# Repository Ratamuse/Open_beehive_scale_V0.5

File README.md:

# Open_beehive_scale_V0.5
Nb_Iot version

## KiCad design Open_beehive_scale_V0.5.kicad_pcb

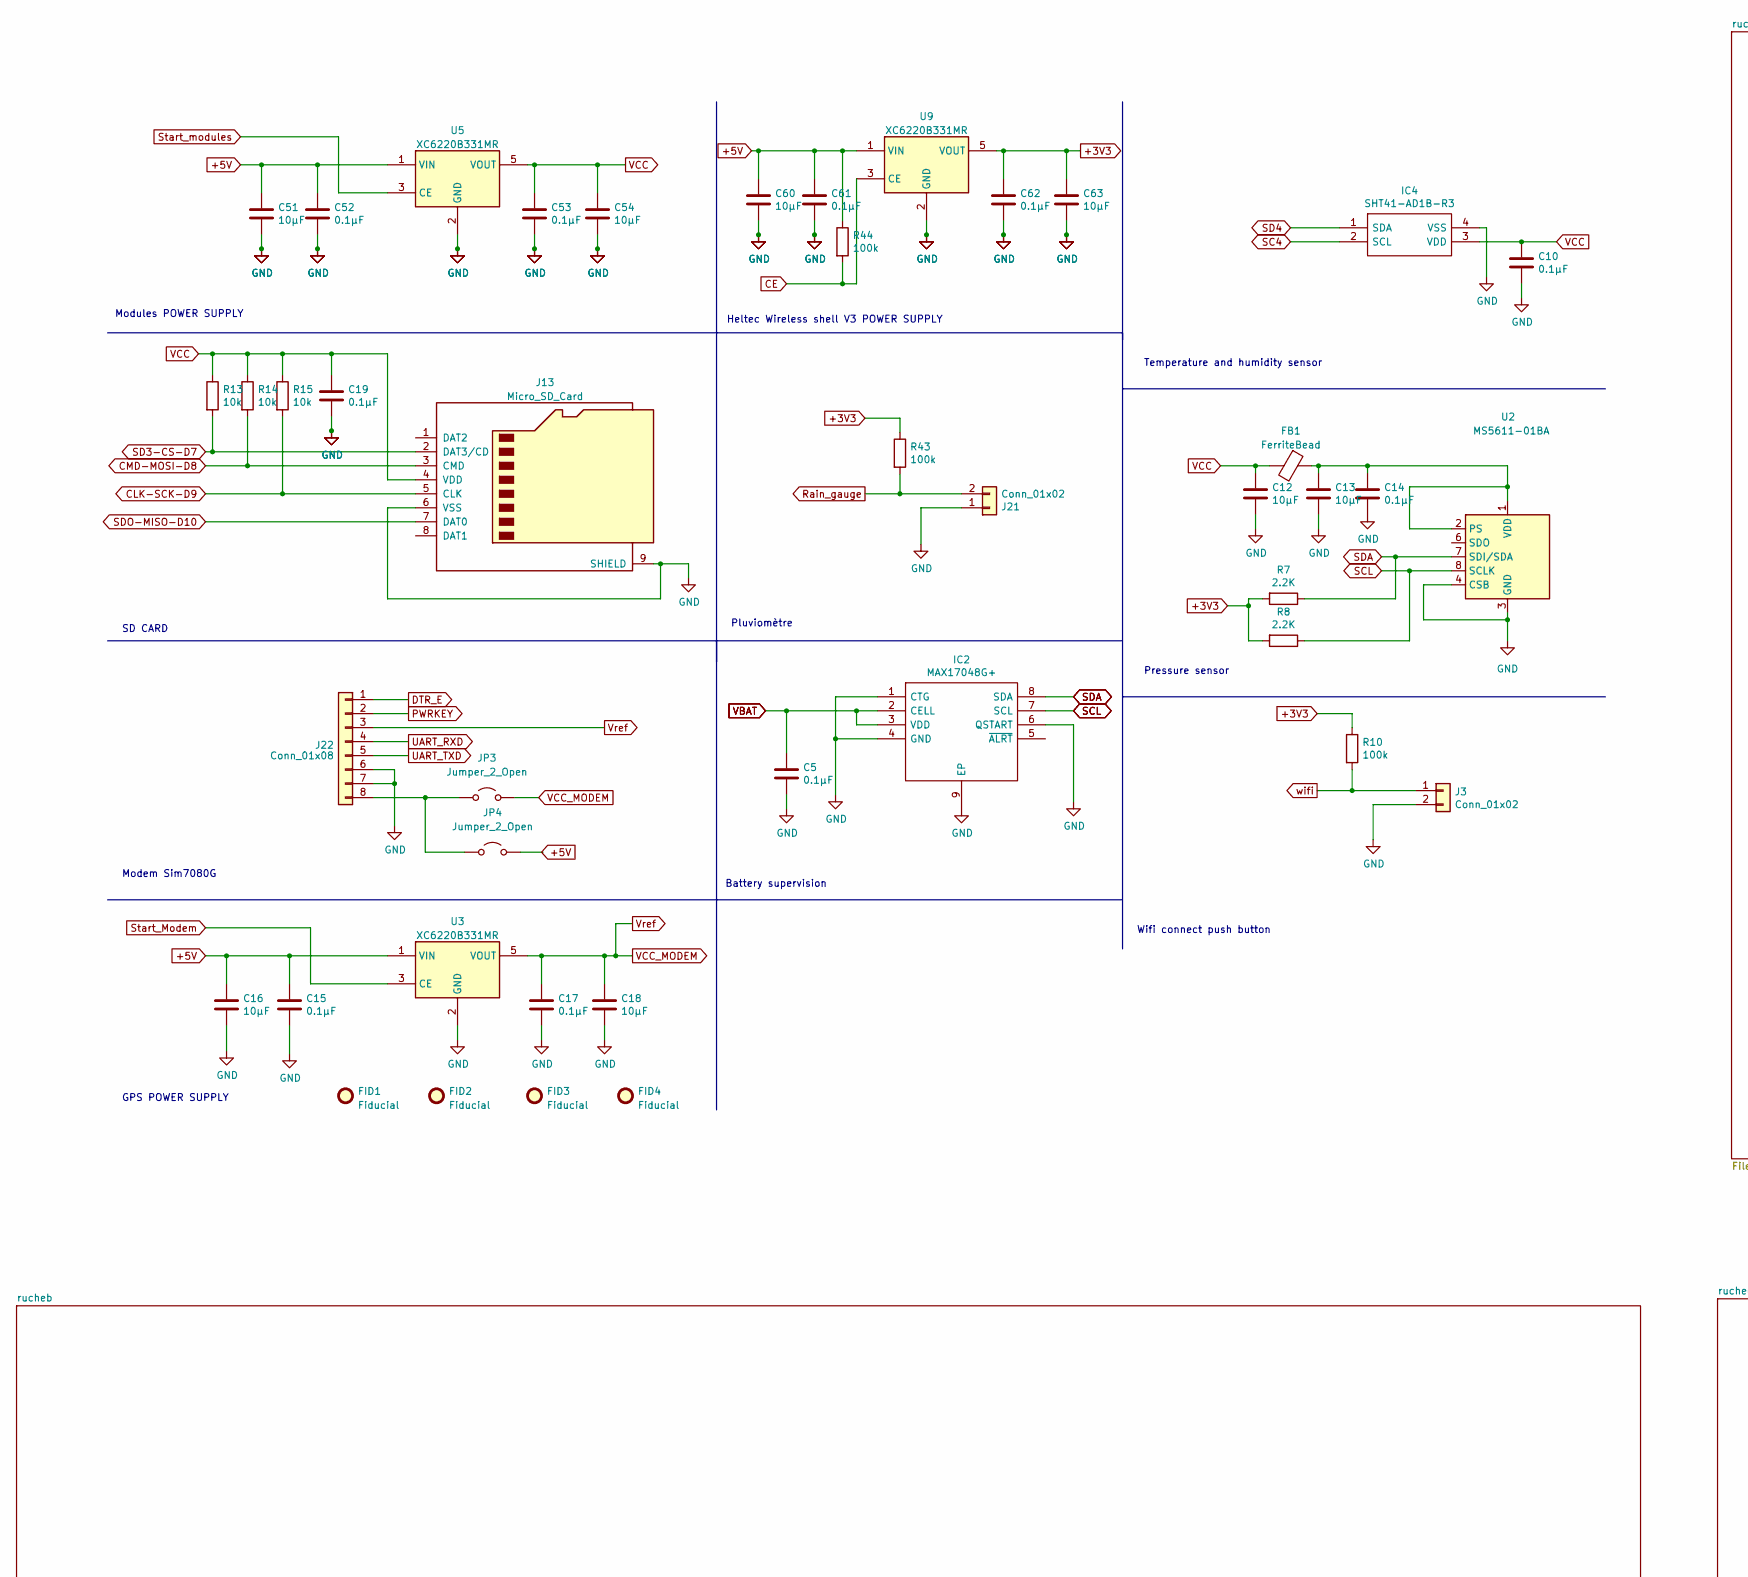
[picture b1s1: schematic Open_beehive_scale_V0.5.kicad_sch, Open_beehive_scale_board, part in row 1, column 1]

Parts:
C5, C10, C14, C17, C19, C52, C53, C61, C62: 0.1µF; C_0603_1608Metric
C12, C13, C18, C51, C54, C60, C63: 10µF; C_0805_2012Metric
C15: 0.1µF; C_0805_2012Metric
C16: 10µF; C_0603_1608Metric
FB1: FerriteBead; R_0603_1608Metric
FID1, FID2, FID3, FID4: Fiducial; Fiducial_1mm_Mask3mm
IC2: MAX17048G+; SON50P200X200X80-9N-D; Manufacturer_Part_Number MAX17048G+; Mouser Part Number 700-MAX17048G+
IC4: SHT41-AD1B-R3; SHT41AD1BR3; Manufacturer_Part_Number SHT41-AD1B-R3; Mouser Part Number 403-SHT41-AD1B-R3
J3, J21: Conn_01x02; 1725656
J13: Micro_SD_Card; microSD_HC_Hirose_DM3AT-SF-PEJM5
J22: Conn_01x08; Sim8070G
JP3, JP4: Jumper_2_Open; SolderJumper-2_P1.3mm_Open_RoundedPad1.0x1.5mm
R7, R8: 2.2K; R_0603_1608Metric
R10, R43, R44: 100k; R_0603_1608Metric
R13, R14, R15: 10k; R_0603_1608Metric
U2: MS5611-01BA; LGA-8_3x5mm_P1.25mm
U3, U5, U9: XC6220B331MR; SOT-23-5

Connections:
+3V3: C62.1, C63.1, R7.2, R8.2, R10.1, R43.1, U9.5 (VOUT); also elsewhere on the board
+5V: C15.1, C16.1, C51.1, C52.1, C60.1, C61.1, JP4.2 (B), R44.1, U3.1 (VIN), U5.1 (VIN), U9.1 (VIN); also elsewhere on the board
CE: R44.2, U9.3 (CE); also elsewhere on the board
CLK-SCK-D9: J13.5 (CLK), R15.2; also elsewhere on the board
CMD-MOSI-D8: J13.3 (CMD), R14.2; also elsewhere on the board
DTR_E: J22.1; also elsewhere on the board
GND: C5.2, C10.2, C12.2, C13.2, C14.2, C15.2, C16.2, C17.2, C18.2, C19.2, C51.2, C52.2, C53.2, C54.2, C60.2, C61.2, C62.2, C63.2, IC2.1 (CTG), IC2.4 (GND), IC2.6 (QSTART), IC2.9 (EP), IC4.4 (VSS), J3.2, J13.6 (VSS), J13.9 (SHIELD), J21.1, J22.6, J22.7, U2.3 (GND), U2.4 (CSB), U2.5 (CSB), U3.2 (GND), U5.2 (GND), U9.2 (GND); also elsewhere on the board
unnamed: J22.8, JP3.1 (A), JP4.1 (A)
unnamed: C13.1, C14.1, FB1.1, U2.1 (VDD), U2.2 (PS)
PWRKEY: J22.2; also elsewhere on the board
Rain_gauge: J21.2, R43.2; also elsewhere on the board
SC4: IC4.2 (SCL); also elsewhere on the board
SCL: IC2.7 (SCL), R8.1, U2.8 (SCLK); also elsewhere on the board
SD3-CS-D7: J13.2 (DAT3/CD), R13.2; also elsewhere on the board
SD4: IC4.1 (SDA); also elsewhere on the board
SDA: IC2.8 (SDA), R7.1, U2.7 (SDI/SDA); also elsewhere on the board
SDO-MISO-D10: J13.7 (DAT0); also elsewhere on the board
Start_Modem: U3.3 (CE); also elsewhere on the board
Start_modules: U5.3 (CE); also elsewhere on the board
UART_RXD: J22.4; also elsewhere on the board
UART_TXD: J22.5; also elsewhere on the board
VBAT: C5.1, IC2.2 (CELL), IC2.3 (VDD); also elsewhere on the board
VCC: C10.1, C12.1, C19.1, C53.1, C54.1, FB1.2, IC4.3 (VDD), J13.4 (VDD), R13.1, R14.1, R15.1, U5.5 (VOUT); also elsewhere on the board
VCC_MODEM: C17.1, C18.1, J22.3, JP3.2 (B), U3.5 (VOUT)
wifi: J3.1, R10.2; also elsewhere on the board

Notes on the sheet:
SD CARD
Pluviomètre
Modem Sim7080G
Battery supervision
Heltec Wireless shell V3 POWER SUPPLY
Wifi connect push button
Temperature and humidity sensor
Pressure sensor
Modules POWER SUPPLY
GPS POWER SUPPLY

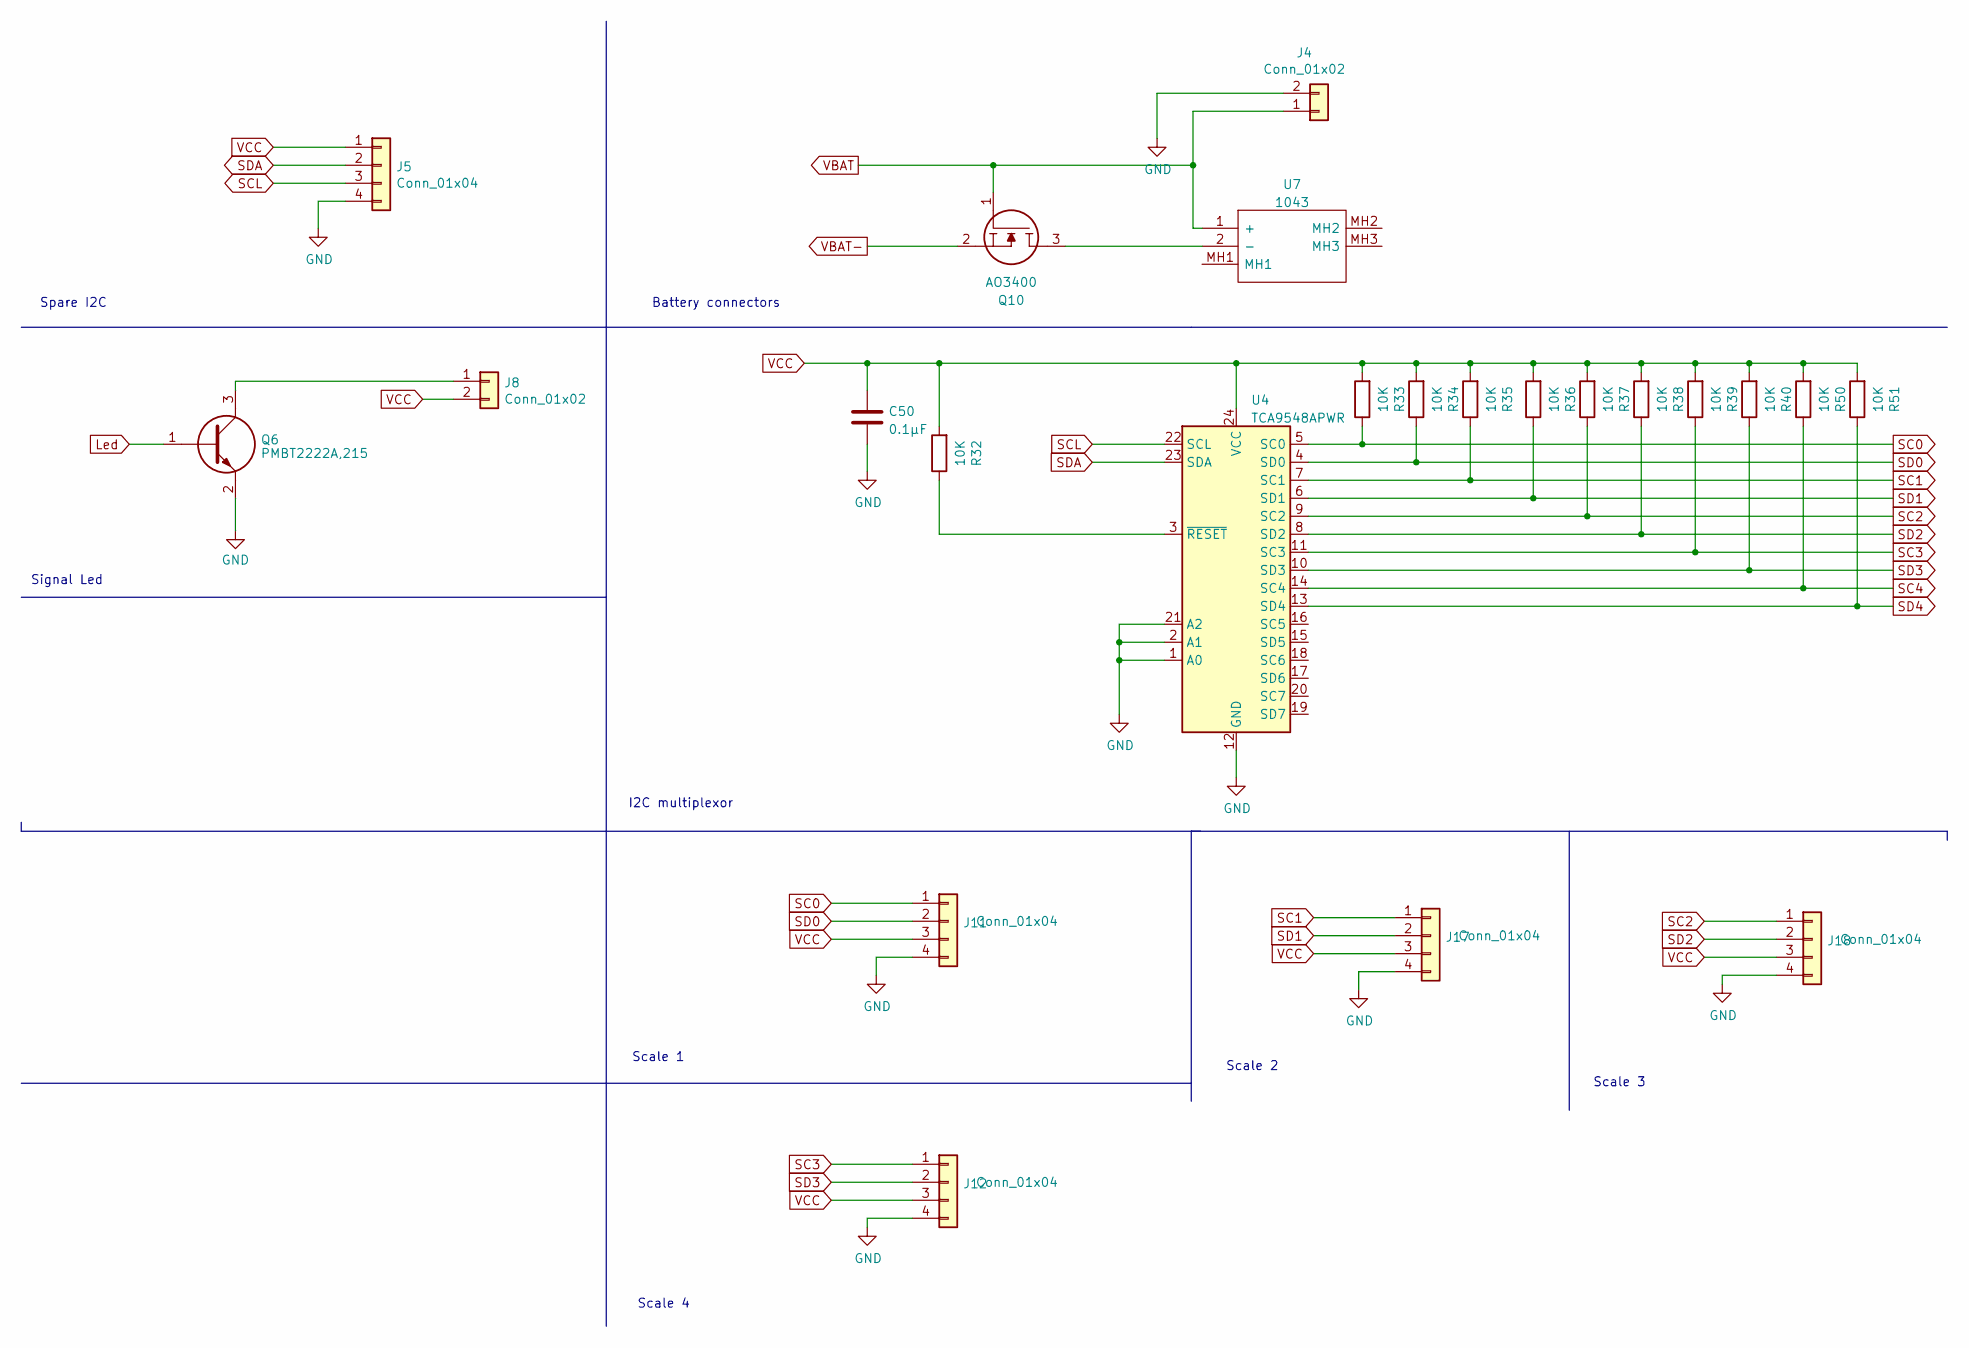
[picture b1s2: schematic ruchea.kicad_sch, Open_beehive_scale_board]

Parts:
C50: 0.1µF; C_0603_1608Metric
J4: Conn_01x02; JST_PH_B2B-PH-K_1x02_P2.00mm_Vertical
J5, J11, J12, J17, J18: Conn_01x04; 1725672
J8: Conn_01x02; 1725656
Q6: PMBT2222A,215; PMBT2222A215; Mouser Part Number 771-PMBT2222A-T/R
Q10: AO3400; SOT-23; Manufacturer_Part_Number AO3400
R32, R33, R34, R35, R36, R37, R38, R39, R40, R50, R51: 10K; R_0603_1608Metric
U4: TCA9548APWR; TSSOP-24_4.4x7.8mm_P0.65mm
U7: 1043; Mouser Part Number 534-1043

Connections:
GND: C50.2, J4.2, J5.4, J11.4, J12.4, J17.4, J18.4, Q6.2, U4.1 (A0), U4.2 (A1), U4.12 (GND), U4.21 (A2); also elsewhere on the board
Led: Q6.1; also elsewhere on the board
unnamed: J8.1, Q6.3
unnamed: R32.1, U4.3 (~RESET)
unnamed: Q10.3, U7.2 (-)
SC0: J11.1, R33.1, U4.5 (SC0)
SC1: J17.1, R35.1, U4.7 (SC1)
SC2: J18.1, R37.1, U4.9 (SC2)
SC3: J12.1, R39.1, U4.11 (SC3)
SC4: R50.1, U4.14 (SC4); also elsewhere on the board
SCL: J5.3, U4.22 (SCL); also elsewhere on the board
SD0: J11.2, R34.1, U4.4 (SD0)
SD1: J17.2, R36.1, U4.6 (SD1)
SD2: J18.2, R38.1, U4.8 (SD2)
SD3: J12.2, R40.1, U4.10 (SD3)
SD4: R51.1, U4.13 (SD4); also elsewhere on the board
SDA: J5.2, U4.23 (SDA); also elsewhere on the board
VBAT: J4.1, Q10.1, U7.1 (+); also elsewhere on the board
VBAT-: Q10.2; also elsewhere on the board
VCC: C50.1, J5.1, J8.2, J11.3, J12.3, J17.3, J18.3, R32.2, R33.2, R34.2, R35.2, R36.2, R37.2, R38.2, R39.2, R40.2, R50.2, R51.2, U4.24 (VCC); also elsewhere on the board

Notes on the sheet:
Scale 4
Scale 1
Scale 3
Scale 2
I2C multiplexor
Battery connectors
Spare I2C
Signal Led

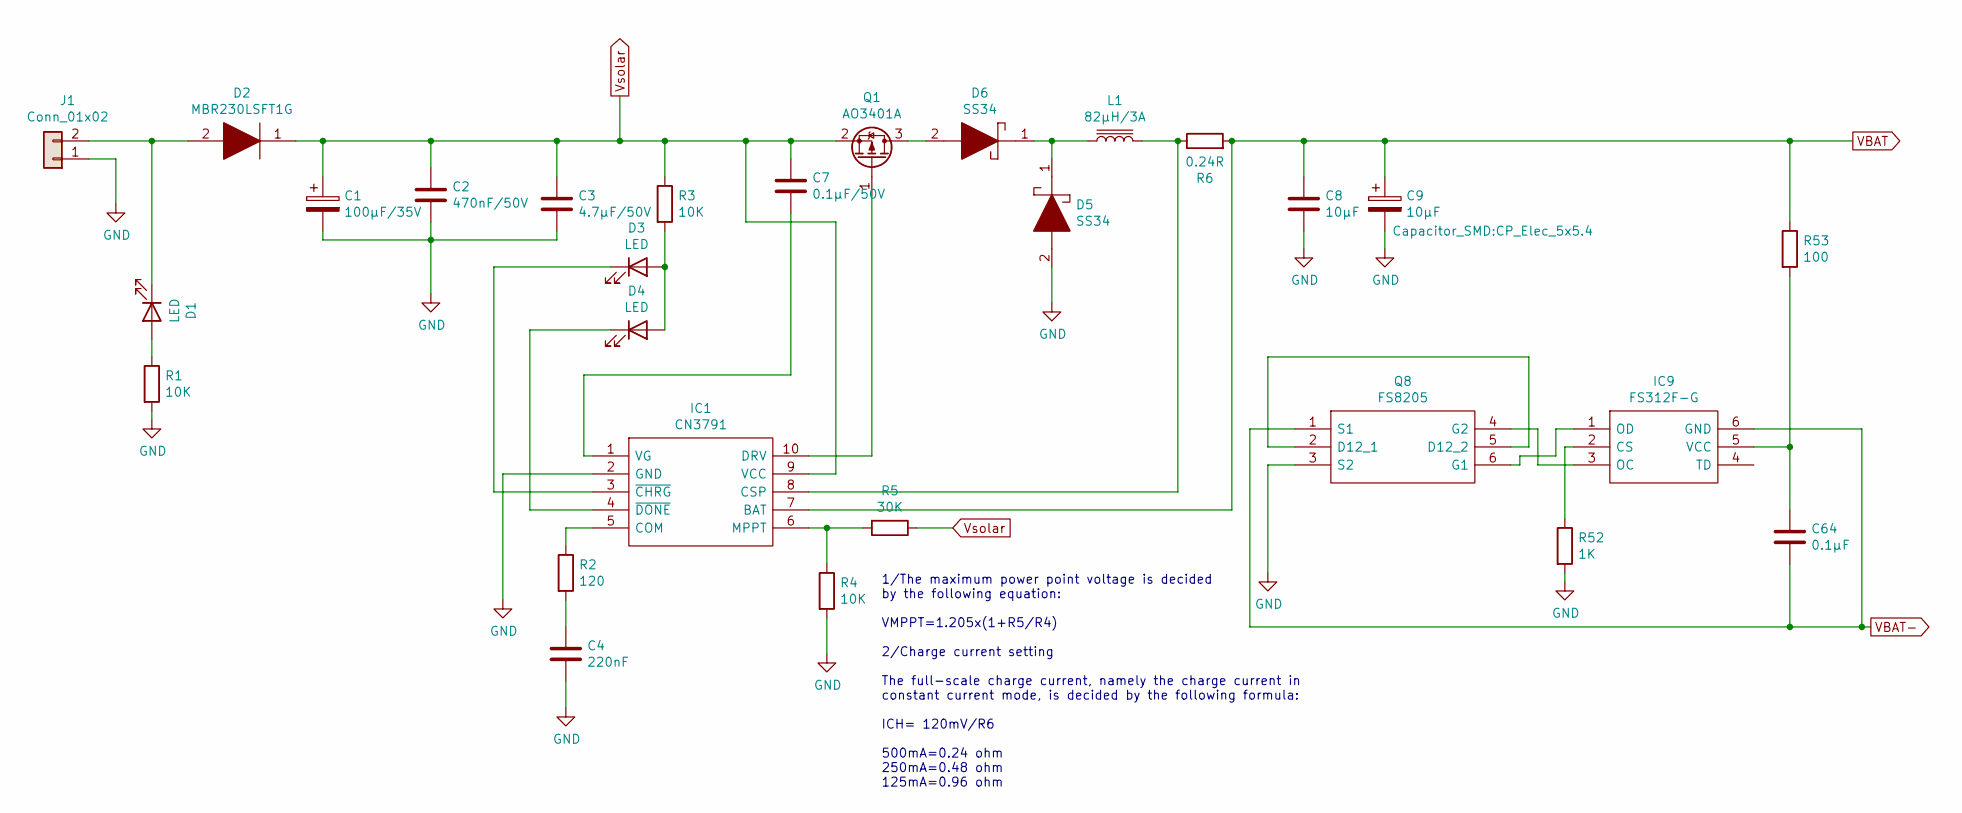
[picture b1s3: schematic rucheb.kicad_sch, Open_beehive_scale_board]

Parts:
C1: 100µF/35V; CP_Elec_6.3x7.7
C2: 470nF/50V; C_0603_1608Metric
C3: 4.7µF/50V; C_0805_2012Metric
C4: 220nF; C_0603_1608Metric
C7: 0.1µF/50V; C_0603_1608Metric
C8: 10µF; C_0805_2012Metric
C9: 10µF; CP_Elec_5x5.4
C64: 0.1µF; C_0603_1608Metric
D1, D3, D4: LED; LED_0603_1608Metric_Pad1.05x0.95mm_HandSolder
D2: MBR230LSFT1G; SODFL3616X98N; Manufacturer_Part_Number MBR230LSFT1G; Mouser Part Number 863-MBR230LSFT1G
D5, D6: SS34; DIOM8059X256N; Manufacturer_Part_Number SS34; Mouser Part Number 512-SS34
IC1: CN3791; SOP100P600X175-10N; Manufacturer_Part_Number CN3791
IC9: FS312F-G; SOT95P280X145-6N; Manufacturer_Part_Number FS312F-G
J1: Conn_01x02; SHDR2W90P0X500_1X2_1060X980X1380P
L1: 82µH/3A; INDPM138126X700N
Q1: AO3401A; SOT-23
Q8: FS8205; Manufacturer_Part_Number FS8205
R1, R3, R4: 10K; R_0603_1608Metric
R2: 120; R_0603_1608Metric
R5: 30K; R_0603_1608Metric
R6: 0.24R; R_2512_6332Metric
R52: 1K; R_0603_1608Metric
R53: 100; R_0603_1608Metric

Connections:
GND: C1.2, C2.2, C3.2, C4.2, C8.2, C9.2, D5.2, IC1.2 (GND), J1.1, Q8.3 (S2), R1.2, R4.2, R52.2; also elsewhere on the board
unnamed: C4.1, R2.2
unnamed: D1.2 (A), R1.1
unnamed: D1.1 (K), D2.2, J1.2
unnamed: D3.2 (A), D4.2 (A), R3.2
unnamed: D3.1 (K), IC1.3 (~CHRG)
unnamed: D4.1 (K), IC1.4 (~DONE)
unnamed: D5.1, D6.1, L1.1
unnamed: IC1.5 (COM), R2.1
unnamed: IC1.8 (CSP), L1.2, R6.1
unnamed: IC1.10 (DRV), Q1.1 (G)
unnamed: IC1.6 (MPPT), R4.1, R5.2
unnamed: C7.2, IC1.1 (VG)
unnamed: IC9.2 (CS), R52.1
unnamed: IC9.3 (OC), Q8.4 (G2)
unnamed: IC9.1 (OD), Q8.6 (G1)
unnamed: C64.1, IC9.5 (VCC), R53.2
unnamed: D6.2, Q1.3 (D)
unnamed: Q8.2 (D12_1), Q8.5 (D12_2)
VBAT: C8.1, C9.1, IC1.7 (BAT), R6.2, R53.1; also elsewhere on the board
VBAT-: C64.2, IC9.6 (GND), Q8.1 (S1); also elsewhere on the board
Vsolar: C1.1, C2.1, C3.1, C7.1, D2.1, IC1.9 (VCC), Q1.2 (S), R3.1, R5.1

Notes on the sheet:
1/The maximum power point voltage is decided by the following equation: VMPPT=1.205x(1+R5/R4) 2/Charge current setting The full-scale charge current, namely the charge current in constant current mode, is decided by the following formula: ICH= 120mV/R6 500mA=0.24 ohm 250mA=0.48 ohm 125mA=0.96 ohm

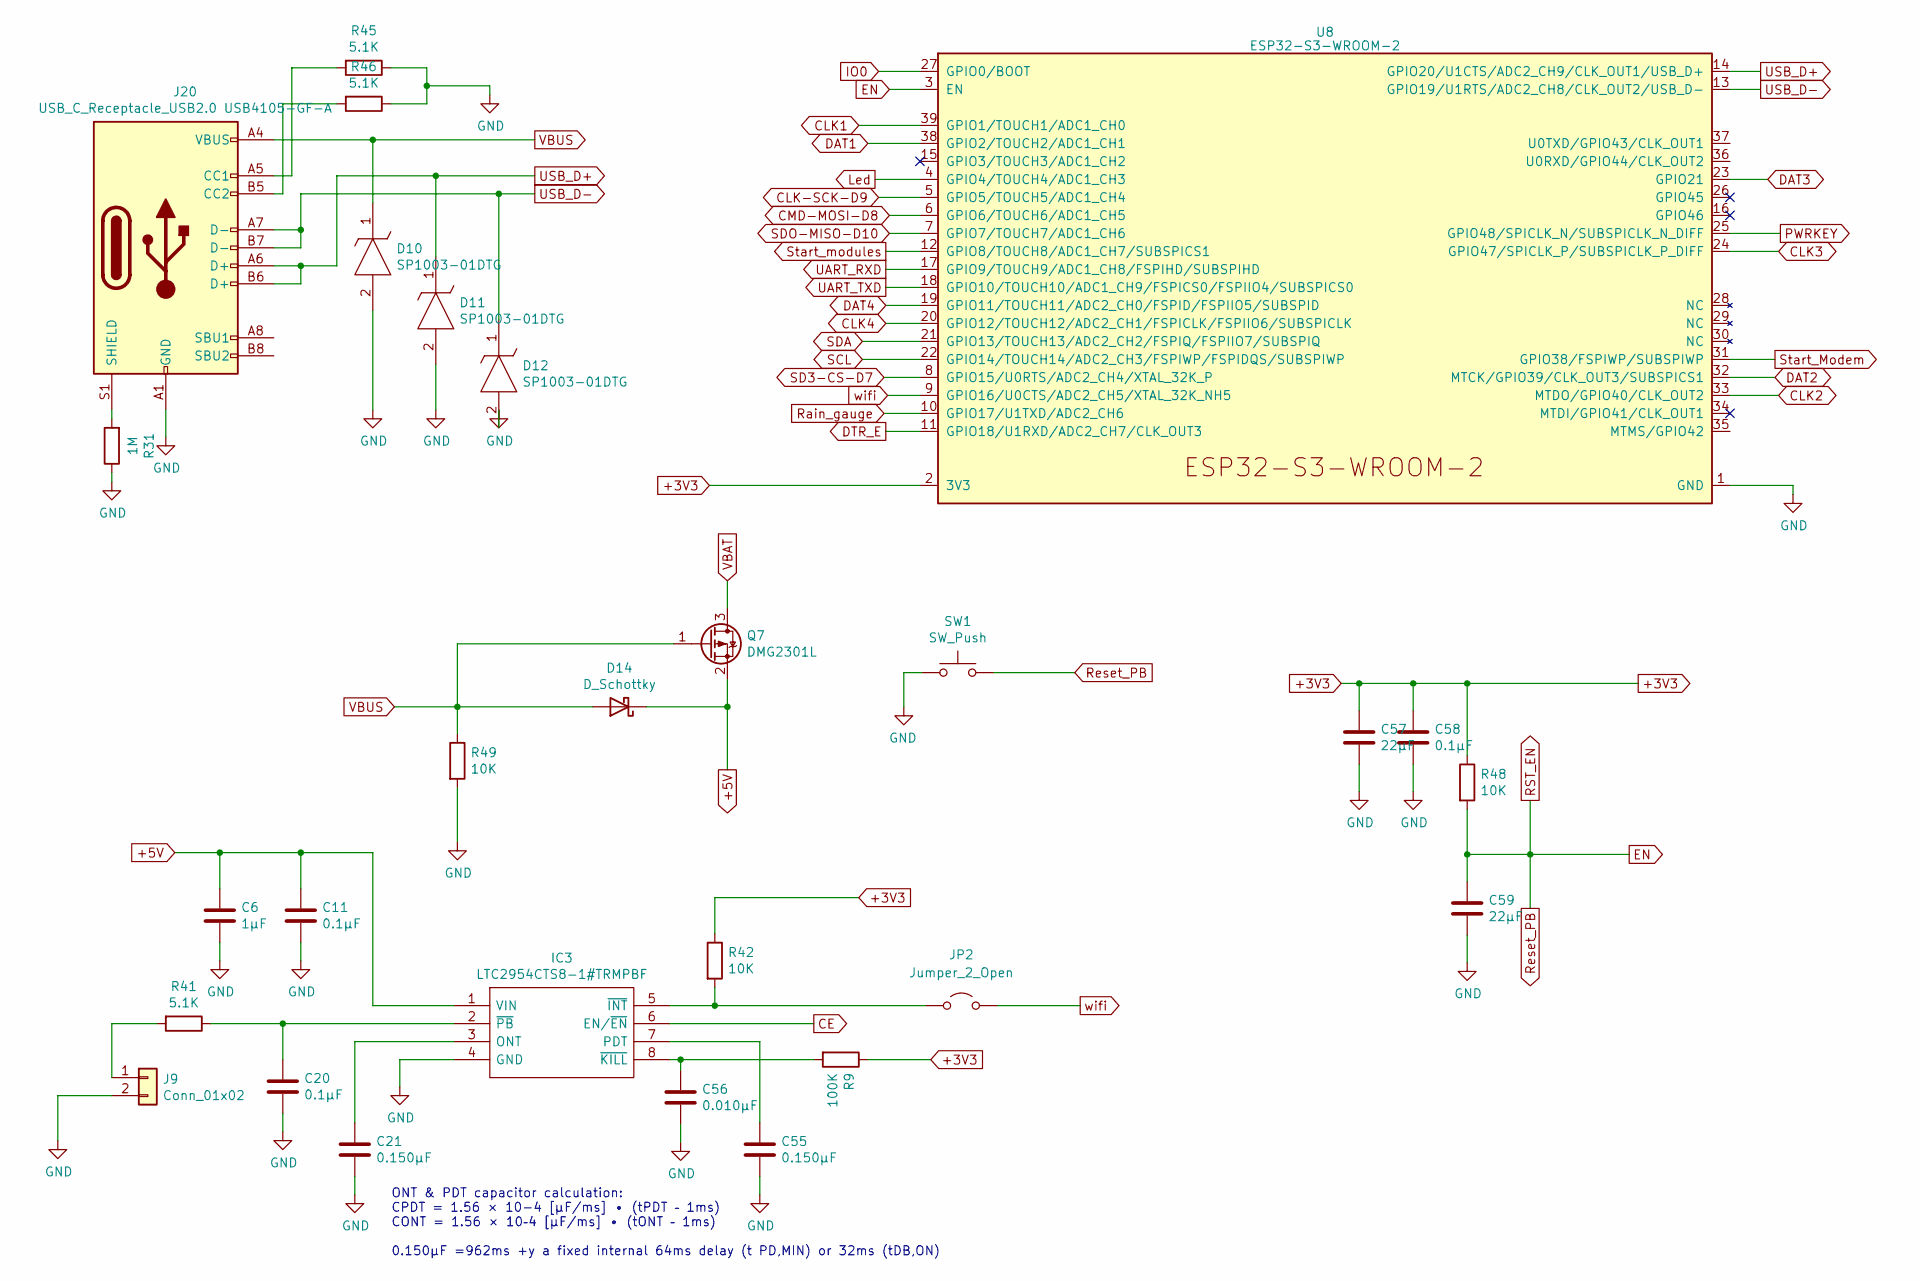
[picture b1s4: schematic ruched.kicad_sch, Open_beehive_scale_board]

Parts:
C6: 1µF; C_0603_1608Metric
C11, C20, C58: 0.1µF; C_0603_1608Metric
C21, C55: 0.150µF; C_0603_1608Metric
C56: 0.010µF; C_0603_1608Metric
C57, C59: 22µF; C_0805_2012Metric
D10, D11, D12: SP1003-01DTG; SODFL1406X65N; Manufacturer_Part_Number SP1003-01DTG; Mouser Part Number 576-SP1003-01DTG
D14: D_Schottky; D_SOD-323
IC3: LTC2954CTS8-1#TRMPBF; SOT65P280X100-8N; Manufacturer_Part_Number LTC2954CTS8-1#TRMPBF; Mouser Part Number 584-C2954CTS8-1TMPF
J9: Conn_01x02; 1725656
J20: USB_C_Receptacle_USB2.0 USB4105-GF-A; TYPE-C-31-M-12
JP2: Jumper_2_Open; SolderJumper-2_P1.3mm_Open_RoundedPad1.0x1.5mm
Q7: DMG2301L; SOT-23
R9: 100K; R_0603_1608Metric
R31: 1M; R_0603_1608Metric
R41, R45, R46: 5.1K; R_0603_1608Metric
R42, R48, R49: 10K; R_0603_1608Metric
SW1: SW_Push; PTS636SL43SMTRLFS
U8: ESP32-S3-WROOM-2

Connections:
+3V3: C57.1, C58.1, R9.1, R42.1, R48.1, U8.2 (3V3); also elsewhere on the board
+5V: C6.1, C11.1, D14.1 (K), IC3.1 (VIN), Q7.2 (S); also elsewhere on the board
CE: IC3.6 (EN/~EN); also elsewhere on the board
CLK1: U8.39 (GPIO1/TOUCH1/ADC1_CH0); also elsewhere on the board
CLK2: U8.33 (MTDO/GPIO40/CLK_OUT2); also elsewhere on the board
CLK3: U8.24 (GPIO47/SPICLK_P/SUBSPICLK_P_DIFF); also elsewhere on the board
CLK4: U8.20 (GPIO12/TOUCH12/ADC2_CH1/FSPICLK/FSPIIO6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); also elsewhere on the board
CLK-SCK-D9: U8.5 (GPIO5/TOUCH5/ADC1_CH4); also elsewhere on the board
CMD-MOSI-D8: U8.6 (GPIO6/TOUCH6/ADC1_CH5); also elsewhere on the board
DAT1: U8.38 (GPIO2/TOUCH2/ADC1_CH1); also elsewhere on the board
DAT2: U8.32 (MTCK/GPIO39/CLK_OUT3/SUBSPICS1); also elsewhere on the board
DAT3: U8.23 (GPIO21); also elsewhere on the board
DAT4: U8.19 (GPIO11/TOUCH11/ADC2_CH0/FSPID/FSPIIO5/S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); also elsewhere on the board
DTR_E: U8.11 (GPIO18/U1RXD/ADC2_CH7/CLK_OUT3); also elsewhere on the board
EN: C59.1, R48.2, SW1.1, U8.3 (EN)
GND: C6.2, C11.2, C20.2, C21.2, C55.2, C56.2, C57.2, C58.2, C59.2, D10.2, D11.2, D12.2, IC3.4 (GND), J9.2, J20.A1 (GND), J20.A12 (GND), J20.B1 (GND), J20.B12 (GND), R31.1, R45.1, R46.1, R49.2, SW1.2, U8.1 (GND), U8.40 (GND), U8.41 (GND); also elsewhere on the board
IO0: U8.27 (GPIO0/BOOT)
Led: U8.4 (GPIO4/TOUCH4/ADC1_CH3); also elsewhere on the board
unnamed: C21.1, IC3.3 (ONT)
unnamed: C55.1, IC3.7 (PDT)
unnamed: IC3.5 (~INT), JP2.1 (A), R42.2
unnamed: C56.1, IC3.8 (~KILL), R9.2
unnamed: C20.1, IC3.2 (~PB), R41.1
unnamed: J9.1, R41.2
unnamed: J20.A5 (CC1), R45.2
unnamed: J20.B5 (CC2), R46.2
unnamed: J20.S1 (SHIELD), R31.2
PWRKEY: U8.25 (GPIO48/SPICLK_N/SUBSPICLK_N_DIFF); also elsewhere on the board
Rain_gauge: U8.10 (GPIO17/U1TXD/ADC2_CH6); also elsewhere on the board
SCL: U8.22 (GPIO14/TOUCH14/ADC2_CH3/FSPIWP/FSPIDQS/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); also elsewhere on the board
SD3-CS-D7: U8.8 (GPIO15/U0RTS/ADC2_CH4/XTAL_32K_P); also elsewhere on the board
SDA: U8.21 (GPIO13/TOUCH13/ADC2_CH2/FSPIQ/FSPIIO7/S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); also elsewhere on the board
SDO-MISO-D10: U8.7 (GPIO7/TOUCH7/ADC1_CH6); also elsewhere on the board
Start_Modem: U8.31 (GPIO38/FSPIWP/SUBSPIWP); also elsewhere on the board
Start_modules: U8.12 (GPIO8/TOUCH8/ADC1_CH7/SUBSPICS1); also elsewhere on the board
UART_RXD: U8.17 (GPIO9/TOUCH9/ADC1_CH8/FSPIHD/SUBSPIHD); also elsewhere on the board
UART_TXD: U8.18 (GPIO10/TOUCH10/ADC1_CH9/FSPICS0/FSPIIO4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); also elsewhere on the board
USB_D+: D11.1, J20.A6 (D+), J20.B6 (D+), U8.14 (GPIO20/U1CTS/ADC2_CH9/CLK_OUT1/USB_D+)
USB_D-: D12.1, J20.A7 (D-), J20.B7 (D-), U8.13 (GPIO19/U1RTS/ADC2_CH8/CLK_OUT2/USB_D-)
VBAT: Q7.3 (D); also elsewhere on the board
VBUS: D10.1, D14.2 (A), J20.A4 (VBUS), J20.A9 (VBUS), J20.B4 (VBUS), J20.B9 (VBUS), Q7.1 (G), R49.1
wifi: JP2.2 (B), U8.9 (GPIO16/U0CTS/ADC2_CH5/XTAL_32K_NH5); also elsewhere on the board

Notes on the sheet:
ONT & PDT capacitor calculation: CPDT = 1.56 × 10-4 [μF/ms] • (tPDT – 1ms) CONT = 1.56 × 10–4 [μF/ms] • (tONT – 1ms) 0.150µF =962ms +y a fixed internal 64ms delay (t PD,MIN) or 32ms (tDB,ON)

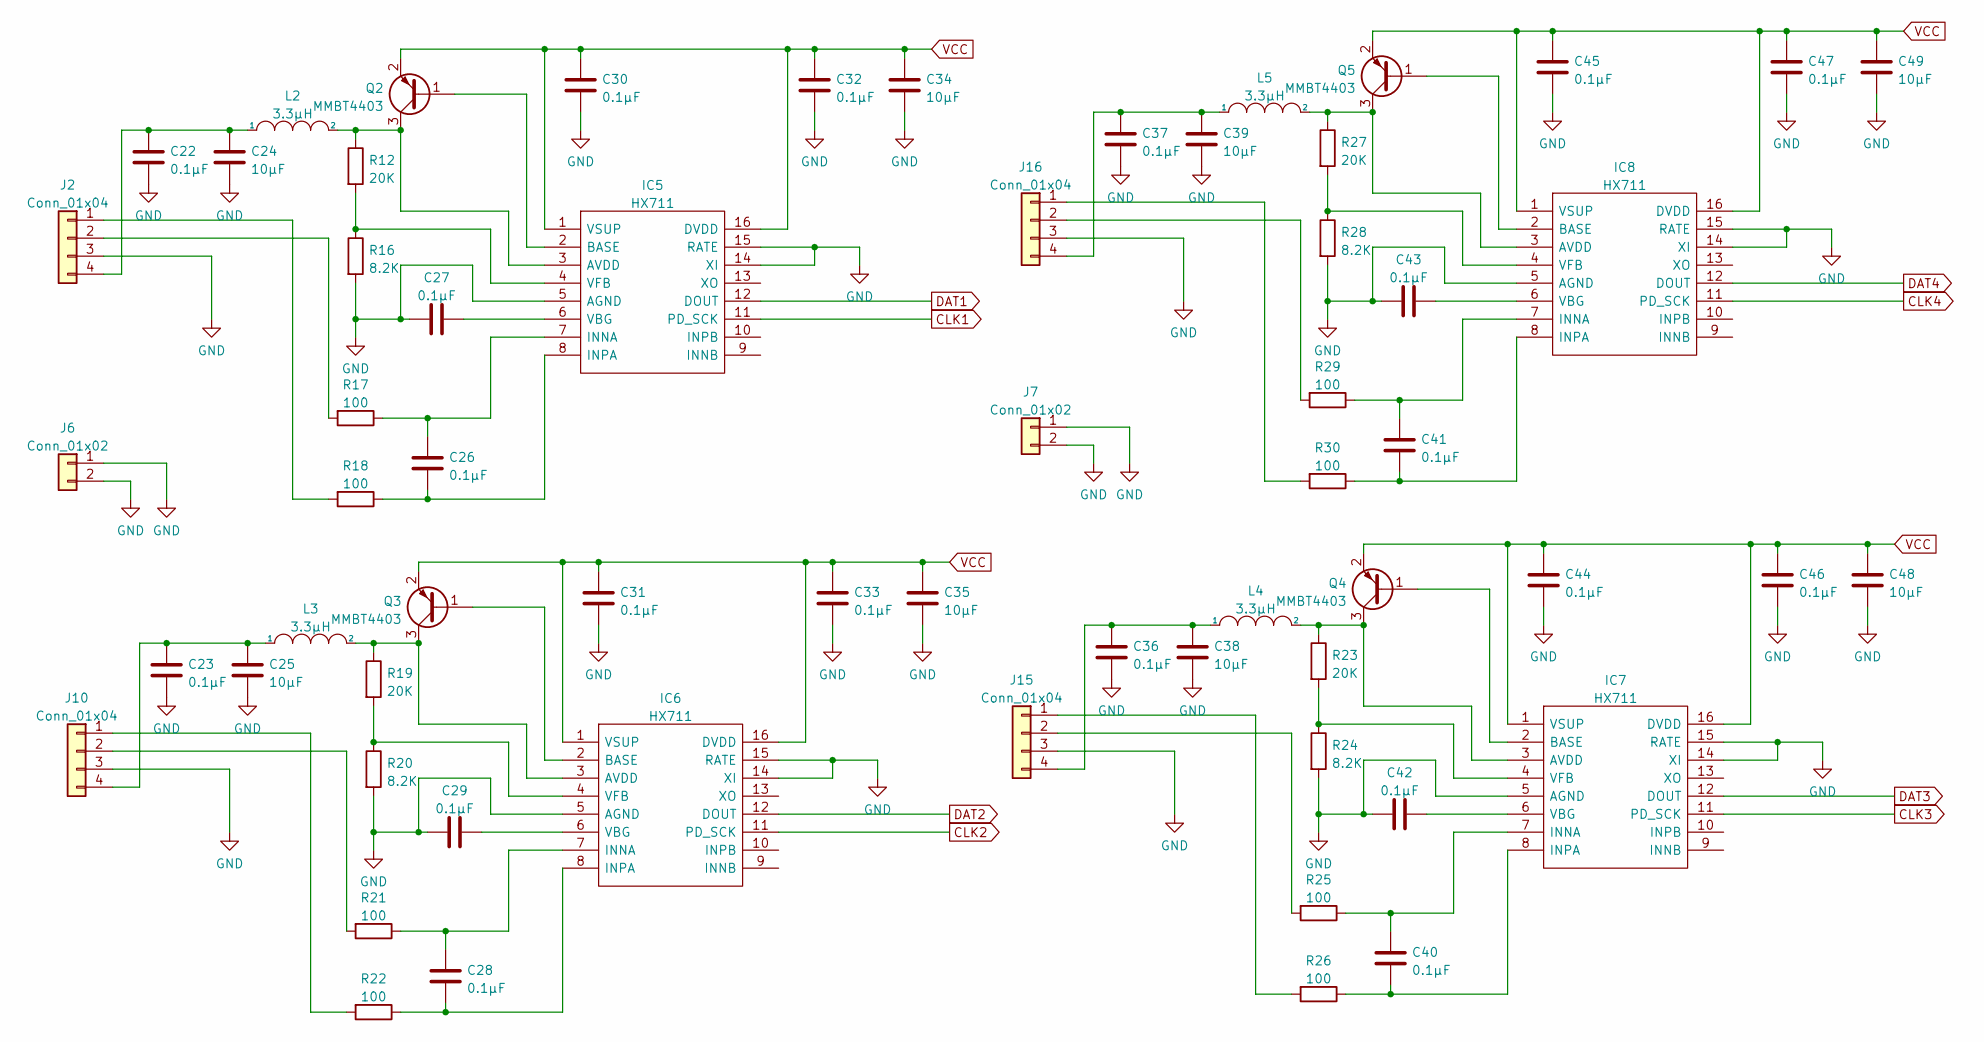
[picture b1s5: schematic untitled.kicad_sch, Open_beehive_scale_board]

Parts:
C22, C23, C26, C27, C28, C29, C30, C31, C32, C33, C36, C37, C40, C41, C42, C43, C44, C45, C46, C47: 0.1µF; C_0603_1608Metric
C24, C25, C34, C35, C38, C39, C48, C49: 10µF; C_0805_2012Metric
IC5, IC6, IC7, IC8: HX711; SOIC127P600X160-16N; Manufacturer_Part_Number HX711
J2, J10, J15, J16: Conn_01x04; 1725672
J6, J7: Conn_01x02; SHDR2W90P0X500_1X2_1060X980X1380P
L2, L3, L4, L5: 3.3µH; L_0603_1608Metric
Q2, Q3, Q4, Q5: MMBT4403; SOT-23
R12, R19, R23, R27: 20K; R_0603_1608Metric
R16, R20, R24, R28: 8.2K; R_0603_1608Metric
R17, R18, R21, R22, R25, R26, R29, R30: 100; R_0603_1608Metric

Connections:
CLK1: IC5.11 (PD_SCK); also elsewhere on the board
CLK2: IC6.11 (PD_SCK); also elsewhere on the board
CLK3: IC7.11 (PD_SCK); also elsewhere on the board
CLK4: IC8.11 (PD_SCK); also elsewhere on the board
DAT1: IC5.12 (DOUT); also elsewhere on the board
DAT2: IC6.12 (DOUT); also elsewhere on the board
DAT3: IC7.12 (DOUT); also elsewhere on the board
DAT4: IC8.12 (DOUT); also elsewhere on the board
GND: C22.2, C23.2, C24.2, C25.2, C27.1, C29.1, C30.2, C31.2, C32.2, C33.2, C34.2, C35.2, C36.2, C37.2, C38.2, C39.2, C42.1, C43.1, C44.2, C45.2, C46.2, C47.2, C48.2, C49.2, IC5.5 (AGND), IC5.14 (XI), IC5.15 (RATE), IC6.5 (AGND), IC6.14 (XI), IC6.15 (RATE), IC7.5 (AGND), IC7.14 (XI), IC7.15 (RATE), IC8.5 (AGND), IC8.14 (XI), IC8.15 (RATE), J2.3, J6.1, J6.2, J7.1, J7.2, J10.3, J15.3, J16.3, R16.2, R20.2, R24.2, R28.2; also elsewhere on the board
unnamed: IC5.3 (AVDD), L2.2, Q2.3 (C), R12.1
unnamed: IC5.2 (BASE), Q2.1 (B)
unnamed: C26.1, IC5.7 (INNA), R17.1
unnamed: C26.2, IC5.8 (INPA), R18.1
unnamed: C27.2, IC5.6 (VBG)
unnamed: IC5.4 (VFB), R12.2, R16.1
unnamed: IC6.3 (AVDD), L3.2, Q3.3 (C), R19.1
unnamed: IC6.2 (BASE), Q3.1 (B)
unnamed: C28.1, IC6.7 (INNA), R21.1
unnamed: C28.2, IC6.8 (INPA), R22.1
unnamed: C29.2, IC6.6 (VBG)
unnamed: IC6.4 (VFB), R19.2, R20.1
unnamed: IC7.3 (AVDD), L4.2, Q4.3 (C), R23.1
unnamed: IC7.2 (BASE), Q4.1 (B)
unnamed: C40.1, IC7.7 (INNA), R25.1
unnamed: C40.2, IC7.8 (INPA), R26.1
unnamed: C42.2, IC7.6 (VBG)
unnamed: IC7.4 (VFB), R23.2, R24.1
unnamed: IC8.3 (AVDD), L5.2, Q5.3 (C), R27.1
unnamed: IC8.2 (BASE), Q5.1 (B)
unnamed: C41.1, IC8.7 (INNA), R29.1
unnamed: C41.2, IC8.8 (INPA), R30.1
unnamed: C43.2, IC8.6 (VBG)
unnamed: IC8.4 (VFB), R27.2, R28.1
unnamed: J2.1, R18.2
unnamed: J2.2, R17.2
unnamed: C22.1, C24.1, J2.4, L2.1
unnamed: J10.1, R22.2
unnamed: J10.2, R21.2
unnamed: C23.1, C25.1, J10.4, L3.1
unnamed: J15.1, R26.2
unnamed: J15.2, R25.2
unnamed: C36.1, C38.1, J15.4, L4.1
unnamed: J16.1, R30.2
unnamed: J16.2, R29.2
unnamed: C37.1, C39.1, J16.4, L5.1
VCC: C30.1, C31.1, C32.1, C33.1, C34.1, C35.1, C44.1, C45.1, C46.1, C47.1, C48.1, C49.1, IC5.1 (VSUP), IC5.16 (DVDD), IC6.1 (VSUP), IC6.16 (DVDD), IC7.1 (VSUP), IC7.16 (DVDD), IC8.1 (VSUP), IC8.16 (DVDD), Q2.2 (E), Q3.2 (E), Q4.2 (E), Q5.2 (E); also elsewhere on the board
